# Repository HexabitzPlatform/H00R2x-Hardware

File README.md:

# H00R20-Hardware
Hexabitz Vertical Extension Module Hardware Design

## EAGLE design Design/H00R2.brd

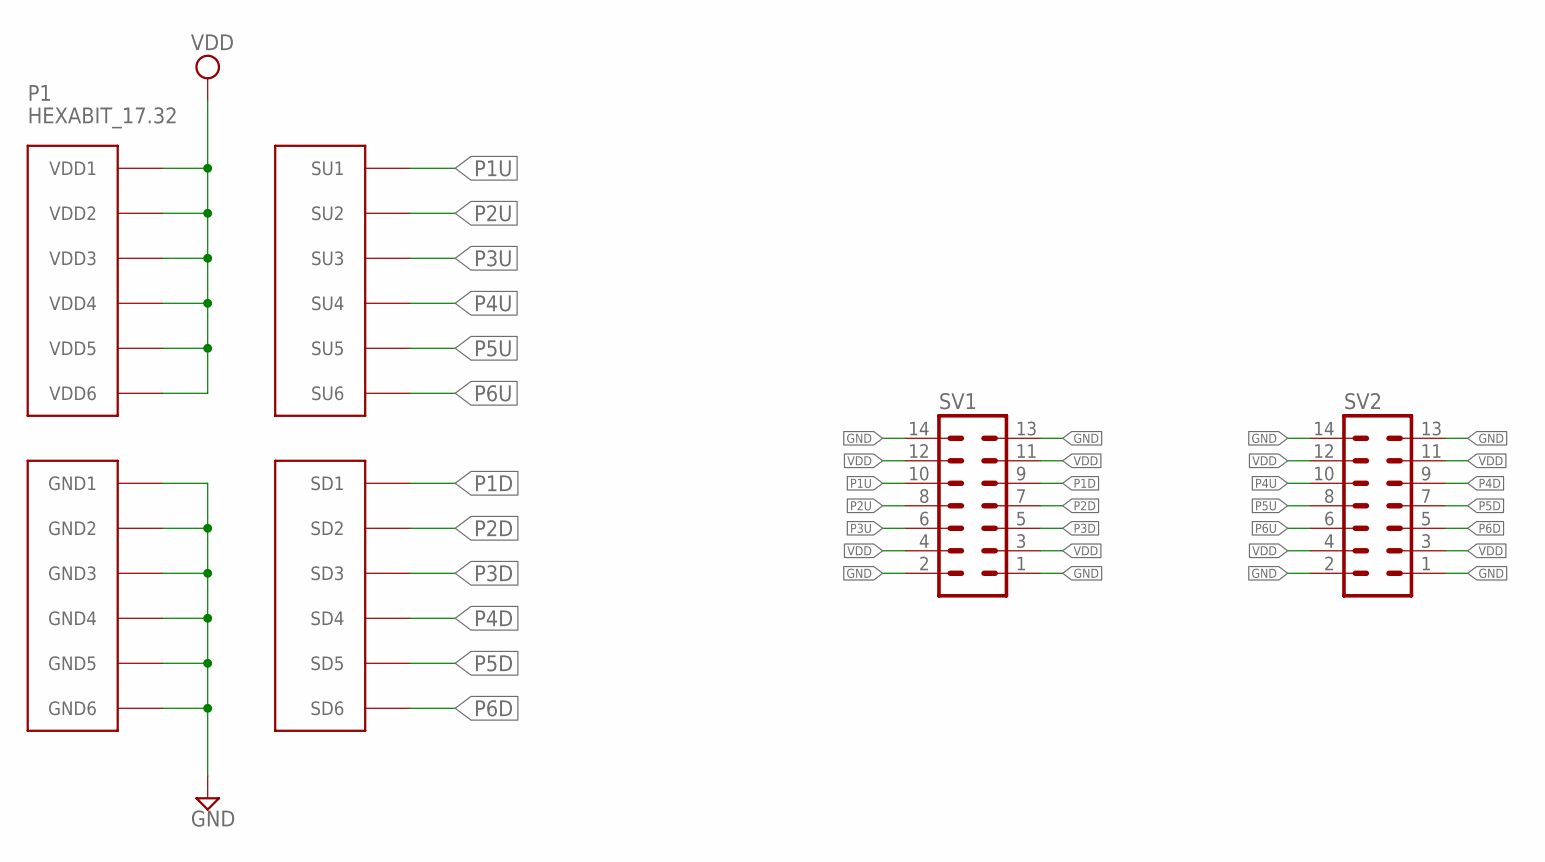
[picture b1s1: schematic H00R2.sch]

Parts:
P1: HEXABIT_17.32
SV1, SV2: MA07-2
TRIMBLE-LOGO1: HEXA-LOGO

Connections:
GND: P1.PAD_PD7 (GND1), P1.PAD_PD8 (GND2), P1.PAD_PD9 (GND3), P1.PAD_PD10 (GND4), P1.PAD_PD11 (GND5), P1.PAD_PD12 (GND6), SV1.1, SV1.2, SV1.13, SV1.14, SV2.1, SV2.2, SV2.13, SV2.14
P1D: P1.PAD_PD1 (SD1), SV1.9
P1U: P1.PAD_PU1 (SU1), SV1.10
P2D: P1.PAD_PD2 (SD2), SV1.7
P2U: P1.PAD_PU2 (SU2), SV1.8
P3D: P1.PAD_PD3 (SD3), SV1.5
P3U: P1.PAD_PU3 (SU3), SV1.6
P4D: P1.PAD_PD4 (SD4), SV2.9
P4U: P1.PAD_PU4 (SU4), SV2.10
P5D: P1.PAD_PD5 (SD5), SV2.7
P5U: P1.PAD_PU5 (SU5), SV2.8
P6D: P1.PAD_PD6 (SD6), SV2.5
P6U: P1.PAD_PU6 (SU6), SV2.6
VDD: P1.PAD_PU7 (VDD1), P1.PAD_PU8 (VDD2), P1.PAD_PU9 (VDD3), P1.PAD_PU10 (VDD4), P1.PAD_PU11 (VDD5), P1.PAD_PU12 (VDD6), SV1.3, SV1.4, SV1.11, SV1.12, SV2.3, SV2.4, SV2.11, SV2.12

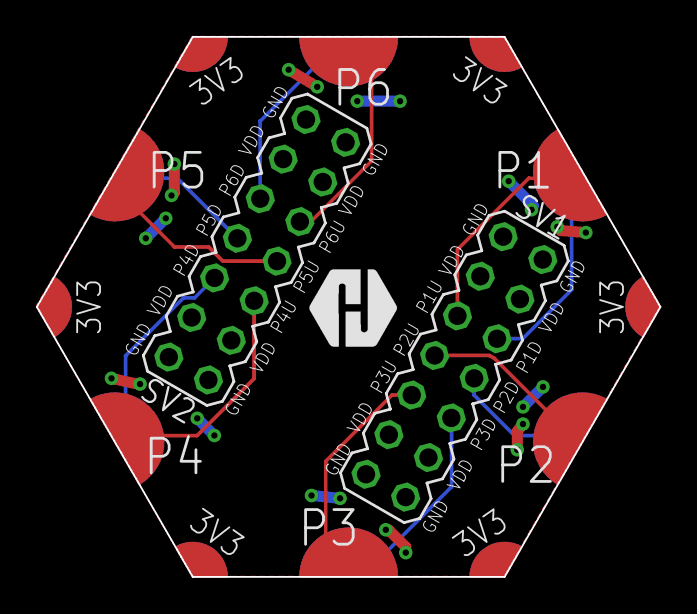
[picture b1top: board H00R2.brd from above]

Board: 2 copper layers, 34.6 x 30.0 mm, 4 parts (0 on the bottom side), 14 nets.

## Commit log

2019-05-23 First release rev 0
2024-03-27 -Update the logo -Improve the layout design
2024-03-27 -Correct some faults
2024-03-27 -Standardize the folder arrangement structure - Fix the Readme file
2024-03-28 -Fix some Schematic issues
2024-03-28 -Copy the placment label of the pin headers to the bottom -Update the hexagon library
